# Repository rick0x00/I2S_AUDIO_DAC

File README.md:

# I2S AUDIO DAC

Module for play sound using I2S

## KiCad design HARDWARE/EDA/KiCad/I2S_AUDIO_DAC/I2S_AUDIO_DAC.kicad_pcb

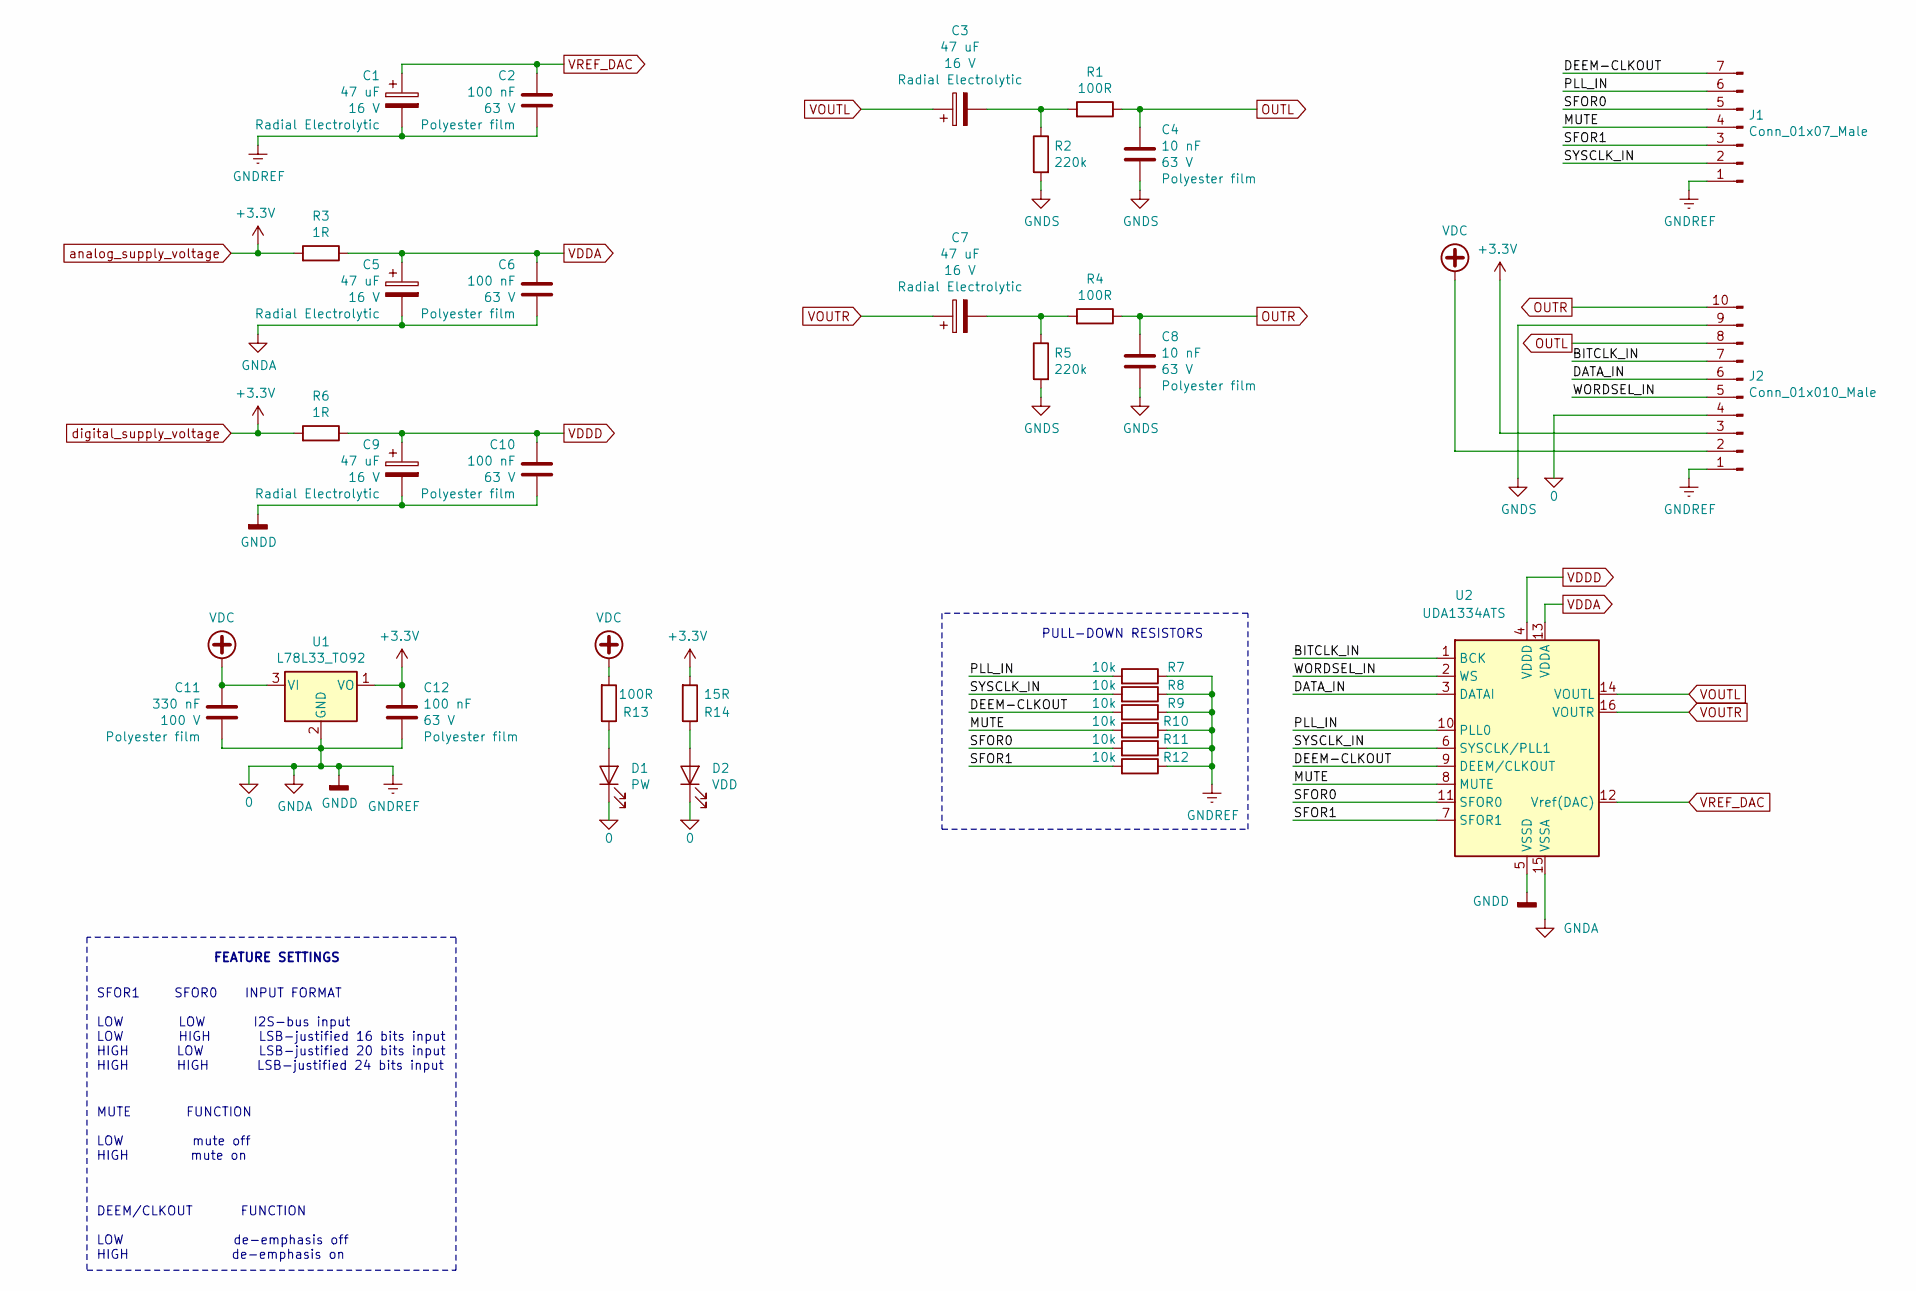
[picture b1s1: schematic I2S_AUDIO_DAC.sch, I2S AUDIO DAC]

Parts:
C1, C3, C5, C7, C9: 47 uF; CP_Radial_D4.0mm_P2.00mm; voltage 16 V
C2, C6, C10, C12: 100 nF; C_Rect_L7.2mm_W2.5mm_P5.00mm_FKS2_FKP2_MKS2_MKP2; voltage 63 V
C4, C8: 10 nF; C_Rect_L7.2mm_W2.5mm_P5.00mm_FKS2_FKP2_MKS2_MKP2; voltage 63 V
C11: 330 nF; C_Rect_L7.2mm_W2.5mm_P5.00mm_FKS2_FKP2_MKS2_MKP2; voltage 100 V
D1: PW; LED_D5.0mm
D2: VDD; LED_D5.0mm
J1: Conn_01x07_Male; PinHeader_1x07_P2.54mm_Horizontal
J2: Conn_01x010_Male; PinHeader_1x10_P2.54mm_Horizontal
R1, R4, R13: 100R; R_Axial_DIN0207_L6.3mm_D2.5mm_P7.62mm_Horizontal
R2, R5: 220k; R_Axial_DIN0207_L6.3mm_D2.5mm_P7.62mm_Horizontal
R3, R6: 1R; R_Axial_DIN0207_L6.3mm_D2.5mm_P7.62mm_Horizontal
R7, R8, R9, R10, R11, R12: 10k; R_Axial_DIN0207_L6.3mm_D2.5mm_P7.62mm_Horizontal
R14: 15R; R_Axial_DIN0207_L6.3mm_D2.5mm_P7.62mm_Horizontal
U1: L78L33_TO92; TO-92_Wide
U2: UDA1334ATS; SSOP-16_4.4x5.2mm_P0.65mm

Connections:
0: C1.2, C2.2, C5.2, C6.2, C9.2, C10.2, C11.2, C12.2, D1.1 (K), D2.1 (K), J1.1, J2.1, J2.4, R7.1, R8.1, R9.1, R10.1, R11.1, R12.1, U1.2 (GND), U2.5 (VSSD), U2.15 (VSSA)
/BITCLK_IN: J2.7, U2.1 (BCK)
/DATA_IN: J2.6, U2.3 (DATAI)
/DEEM-CLKOUT: J1.7, R9.2, U2.9 (DEEM/CLKOUT)
/MUTE: J1.4, R10.2, U2.8 (MUTE)
/PLL_IN: J1.6, R7.2, U2.10 (PLL0)
/SFOR0: J1.5, R11.2, U2.11 (SFOR0)
/SFOR1: J1.3, R12.2, U2.7 (SFOR1)
/SYSCLK_IN: J1.2, R8.2, U2.6 (SYSCLK/PLL1)
/WORDSEL_IN: J2.5, U2.2 (WS)
GNDS: C4.1, C8.1, J2.9, R2.2, R5.2
unnamed: C3.2, R1.2, R2.1
unnamed: C7.2, R4.2, R5.1
unnamed: D1.2 (A), R13.1
unnamed: D2.2 (A), R14.1
OUTL: C4.2, J2.8, R1.1
OUTR: C8.2, J2.10, R4.1
VDC: C11.1, J2.2, R13.2, U1.3 (VI)
VDDA: C5.1, C6.1, R3.1, U2.13 (VDDA)
VDDD: C9.1, C10.1, R6.1, U2.4 (VDDD)
VOUTL: C3.1, U2.14 (VOUTL)
VOUTR: C7.1, U2.16 (VOUTR)
VREF_DAC: C1.1, C2.1, U2.12 (Vref(DAC))
analog_supply_voltage: C12.1, J2.3, R3.2, R6.2, R14.2, U1.1 (VO)

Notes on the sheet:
PULL-DOWN RESISTORS
SFOR1 SFOR0 INPUT FORMAT LOW LOW I2S-bus input LOW HIGH LSB-justified 16 bits input HIGH LOW LSB-justified 20 bits input HIGH HIGH LSB-justified 24 bits input
MUTE FUNCTION LOW mute off HIGH mute on
DEEM/CLKOUT FUNCTION LOW de-emphasis off HIGH de-emphasis on
FEATURE SETTINGS

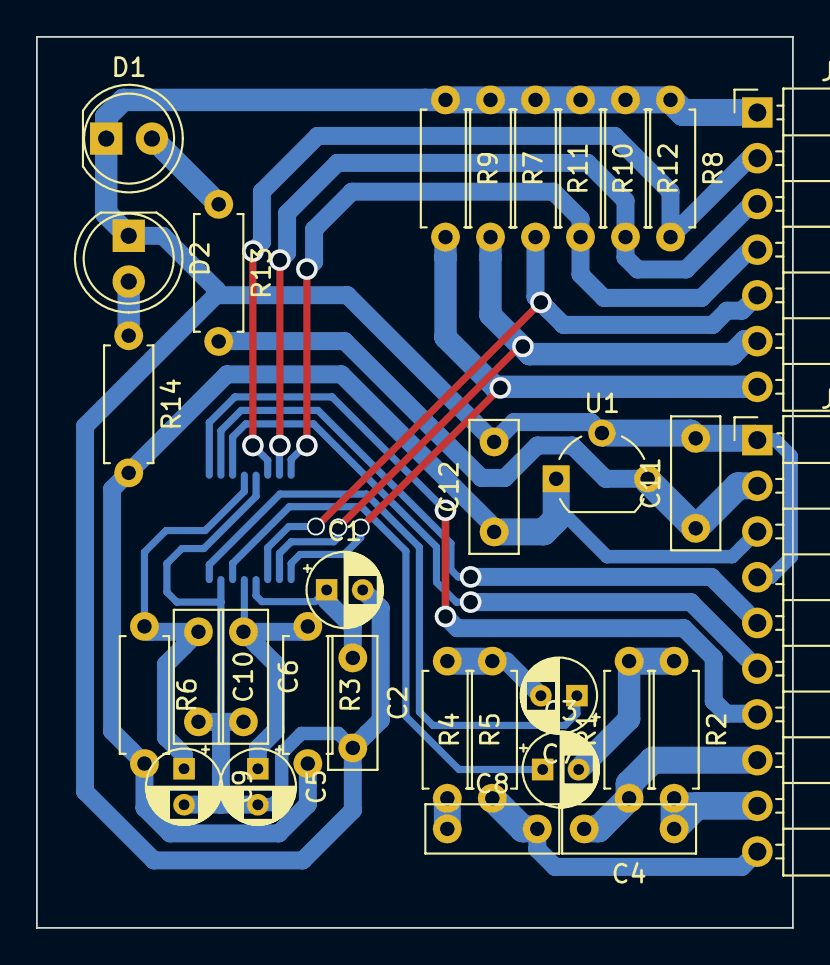
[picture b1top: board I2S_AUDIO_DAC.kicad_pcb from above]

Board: 2 copper layers, 42.0 x 49.5 mm, 32 parts (1 on the bottom side), 24 nets.

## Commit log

2021-12-08 create architecture files
2021-12-08 create kicad files
2021-12-08 Fisihed Schematic
2021-12-09 test mult push
2021-12-09 pause work
2021-12-09 add led to schematic and adjust pcb
2021-12-10 pcb finished
2021-12-10 psb page sheet configured
2021-12-10 add images to project
2021-12-10 add images to readme
2021-12-10 add images to readme gitlab
2021-12-10 add images to readme gitlab and github
